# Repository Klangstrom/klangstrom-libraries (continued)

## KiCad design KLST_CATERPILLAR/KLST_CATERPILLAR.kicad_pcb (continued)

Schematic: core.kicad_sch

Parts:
C5, C10, C16, C28: 1uF; C_0402_1005Metric; JLCPCB C52923
C6, C7, C8, C11, C12, C14, C15, C17, C18, C19, C20, C21, C22, C23, C25: 100nF; C_0402_1005Metric; JLCPCB C1525
C9, C13: 12pF; C_0402_1005Metric; JLCPCB C1547
C24, C27: 2.2uF; C_0402_1005Metric; JLCPCB C107370
C26: 4.7uF; C_0402_1005Metric; JLCPCB C23733
D3: PWR_LED; LED_0805_2012Metric; JLCPCB C34499
R7: 10R; R_0402_1005Metric; JLCPCB C25077
R8: 1K; R_0805_2012Metric_Pad1.20x1.40mm_HandSolder; JLCPCB C17513
R9, R10, R11: 10K; R_0402_1005Metric; JLCPCB C25744
SW1: BUTTON_RESET; SW_Push_SPST_NO_Alps_SKRK; JLCPCB C115357
SW2: BUTTON_BOOT_FLASH; SW_Push_SPST_NO_Alps_SKRK; JLCPCB C115357
U2: STM32H723ZGTx; LQFP-144_20x20mm_P0.5mm; JLCPCB C730146
Y1: 16MHz; Crystal_SMD_3225-4Pin_3.2x2.5mm; JLCPCB C13738

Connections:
+3.3VA: C5.1, C7.1, C10.1, C12.1, U2.32 (VREF+), U2.33 (VDDA); also elsewhere on the board
/core/(PWR_LED): D3.1 (K), R8.2
/core/_PDR_ON: R10.2, U2.143 (PDR_ON)
/core/_VCAP_1: C24.1, U2.71 (VCAP)
/core/_VCAP_2: C27.1, U2.106 (VCAP)
BOOT0: R11.2, SW2.1, U2.138 (BOOT0)
GPIO_00_PWM: U2.13 (PF3); also elsewhere on the board
GPIO_02_PWM: U2.11 (PF1); also elsewhere on the board
GPIO_03_PWM: U2.10 (PF0); also elsewhere on the board
GPIO_04_ADC: U2.53 (PF13); also elsewhere on the board
GPIO_05_ADC: U2.49 (PF11); also elsewhere on the board
GPIO_06: U2.80 (PD11); also elsewhere on the board
GPIO_07: U2.14 (PF4); also elsewhere on the board
GPIO_08: U2.9 (PC15); also elsewhere on the board
GPIO_09: U2.8 (PC14); also elsewhere on the board
GPIO_10: U2.7 (PC13); also elsewhere on the board
GPIO_11: U2.134 (PB4(NJTRST)); also elsewhere on the board
GPIO_12: U2.118 (PD4); also elsewhere on the board
GPIO_13: U2.90 (PG5); also elsewhere on the board
GPIO_14: U2.89 (PG4); also elsewhere on the board
GPIO_15: U2.88 (PG3); also elsewhere on the board
GPIO_16: U2.87 (PG2); also elsewhere on the board
GPIO_17: U2.67 (PE14); also elsewhere on the board
GPIO_18: U2.117 (PD3); also elsewhere on the board
I2C_USR_SCL: U2.136 (PB6); also elsewhere on the board
I2C_USR_SDA: U2.137 (PB7); also elsewhere on the board
NRST: C25.1, R9.1, SW1.2, U2.25 (NRST); also elsewhere on the board
unnamed: C13.1, R7.2, Y1.3
SERIAL_USR_RX: U2.37 (PA3); also elsewhere on the board
SERIAL_USR_TX: U2.119 (PD5); also elsewhere on the board
SPI_USR_CS: U2.3 (PE4); also elsewhere on the board
SPI_USR_MISO: U2.4 (PE5); also elsewhere on the board
SPI_USR_MOSI: U2.5 (PE6); also elsewhere on the board
SPI_USR_SCK: U2.1 (PE2); also elsewhere on the board
_ADC_USR: U2.15 (PF5)
_AUDIO_CODEC_I2C_SCL: U2.54 (PF14); also elsewhere on the board
_AUDIO_CODEC_I2C_SDA: U2.55 (PF15); also elsewhere on the board
_AUDIO_CODEC_SAI_FS: U2.21 (PF9); also elsewhere on the board
_AUDIO_CODEC_SAI_MCLK: U2.19 (PF7); also elsewhere on the board
_AUDIO_CODEC_SAI_SCK: U2.20 (PF8); also elsewhere on the board
_AUDIO_CODEC_SAI_SD_IN: U2.48 (PB2); also elsewhere on the board
_AUDIO_CODEC_SAI_SD_OUT: U2.2 (PE3); also elsewhere on the board
_AUDIO_MIC_CLK: U2.28 (PC2_C); also elsewhere on the board
_AUDIO_MIC_DATA: U2.29 (PC3_C); also elsewhere on the board
_BUTTON_PROGRAMMER: U2.50 (PF12); also elsewhere on the board
_CARD_SDMMC_CK: U2.122 (PD6); also elsewhere on the board
_CARD_SDMMC_CMD: U2.123 (PD7); also elsewhere on the board
_CARD_SDMMC_D0: U2.124 (PG9); also elsewhere on the board
_CARD_SDMMC_D1: U2.125 (PG10); also elsewhere on the board
_CARD_SDMMC_D2: U2.126 (PG11); also elsewhere on the board
_CARD_SDMMC_D3: U2.127 (PG12); also elsewhere on the board
_DAC_USR: U2.40 (PA4)
_DISPLAY_BACKLIGHT_PWM: U2.98 (PC8)
_DISPLAY_LTDC_B0: U2.129 (PG14)
_DISPLAY_LTDC_B1: U2.114 (PD0)
_DISPLAY_LTDC_B2: U2.116 (PD2)
_DISPLAY_LTDC_B3: U2.79 (PD10)
_DISPLAY_LTDC_B4: U2.65 (PE12)
_DISPLAY_LTDC_B5: U2.135 (PB5)
_DISPLAY_LTDC_B6: U2.139 (PB8)
_DISPLAY_LTDC_B7: U2.140 (PB9)
_DISPLAY_LTDC_CLK: U2.92 (PG7)
_DISPLAY_LTDC_DE: U2.66 (PE13)
_DISPLAY_LTDC_G0: U2.47 (PB1)
_DISPLAY_LTDC_G1: U2.46 (PB0)
_DISPLAY_LTDC_G2: U2.42 (PA6)
_DISPLAY_LTDC_G3: U2.99 (PC9)
_DISPLAY_LTDC_G4: U2.69 (PB10)
_DISPLAY_LTDC_G5: U2.27 (PC1)
_DISPLAY_LTDC_G6: U2.97 (PC7)
_DISPLAY_LTDC_G7: U2.93 (PG8)
_DISPLAY_LTDC_HSYNC: U2.96 (PC6)
_DISPLAY_LTDC_R0: U2.128 (PG13)
_DISPLAY_LTDC_R1: U2.36 (PA2)
_DISPLAY_LTDC_R2: U2.111 (PC10)
_DISPLAY_LTDC_R3: U2.110 (PA15(JTDI))
_DISPLAY_LTDC_R4: U2.41 (PA5)
_DISPLAY_LTDC_R5: U2.26 (PC0)
_DISPLAY_LTDC_R6: U2.113 (PC12)
_DISPLAY_LTDC_R7: U2.68 (PE15)
_DISPLAY_LTDC_VSYNC: U2.43 (PA7)
_DISPLAY_ON_OFF: U2.44 (PC4)
_DISPLAY_TOUCH_INTERRUPT: U2.82 (PD13)
_ENCODER_00_A: U2.100 (PA8)
_ENCODER_00_B: U2.64 (PE11)
_ENCODER_00_BUTTON: U2.102 (PA10)
_ENCODER_01_A: U2.34 (PA0)
_ENCODER_01_B: U2.35 (PA1)
_ENCODER_01_BUTTON: U2.70 (PB11)
_EXT_MEMORY_A0: U2.73 (PB12)
_EXT_MEMORY_A1: U2.81 (PD12)
_EXT_MEMORY_A2: U2.74 (PB13)
_EXT_MEMORY_A3: U2.18 (PF6)
_EXT_MEMORY_A4: U2.58 (PE7)
_EXT_MEMORY_A5: U2.59 (PE8)
_EXT_MEMORY_A6: U2.60 (PE9)
_EXT_MEMORY_A7: U2.63 (PE10)
_EXT_MEMORY_CHIP_SELECT: U2.91 (PG6)
_EXT_MEMORY_CLK: U2.22 (PF10)
_EXT_MEMORY_DQS: U2.45 (PC5)
_IDC_SERIAL_00_RX: U2.141 (PE0); also elsewhere on the board
_IDC_SERIAL_00_TX: U2.142 (PE1); also elsewhere on the board
_IDC_SERIAL_01_RX: U2.56 (PG0)
_IDC_SERIAL_01_TX: U2.57 (PG1)
_LED_00: U2.75 (PB14); also elsewhere on the board
_LED_01: U2.76 (PB15); also elsewhere on the board
_MECH_BUTTON_00: U2.85 (PD14)
_MECH_BUTTON_01: U2.86 (PD15)
_MIDI_ANALOG_IN: U2.112 (PC11)
_MIDI_ANALOG_OUT: U2.115 (PD1)
_RCC_OSC_IN: C9.2, U2.23 (PH0), Y1.1
_RCC_OSC_OUT: R7.1, U2.24 (PH1)
_SERIAL_DEBUG_RX: U2.78 (PD9); also elsewhere on the board
_SERIAL_DEBUG_TX: U2.77 (PD8); also elsewhere on the board
_SWD_IO: U2.105 (PA13(JTMS)); also elsewhere on the board
_SWD_OUT: U2.133 (PB3(JTDO)); also elsewhere on the board
_USB_DEVICE_HOST_N: U2.103 (PA11); also elsewhere on the board
_USB_DEVICE_HOST_P: U2.104 (PA12); also elsewhere on the board
_USB_DEVICE_HOST_VBUS: U2.101 (PA9); also elsewhere on the board

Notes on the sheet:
CAP SPECS: CL=2*(CLOAD_XTAL-CPARASITIC) example: 12pF=2*(9pF-3pF)
@TODO(@maybe get rid of buttons)
VBAT: 1 μF ceramic and 100 nF close to the VBAT pin
@TODO(maybe PIN out fot GPIOs THT:C79866 or SMD:C601974/C2829932)
VDDA: 1 μF ceramic and 100 nF as close as possible of the pin.
press at startup for DFU mode. this is however usually done in software i.e this button is only necessary if something goes wrong
VDD1–11: 100 nF ceramic, for each VDD as close as possible of the pins. A 4.7 μF ceramic connected to one of the VDD pin.
PDR_ON tied to VDD = Power-on reset (POR) and power-down reset (PDR) circuit switched ON
MCU_POWER
BUTTON_RESET
@NOTE(close to MCU)
MCU
BUTTON_BOOT_FLASH
XTAL
POWER-LED

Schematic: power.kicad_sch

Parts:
C1, C2, C88, C89: 10uF; C_0805_2012Metric; JLCPCB C15850
C3, C69: 1uF; C_0805_2012Metric; JLCPCB C28323
C4, C71: 10nF; C_0805_2012Metric; JLCPCB C1710
FB1, FB4: 600Ω@100MHz; L_1206_3216Metric; JLCPCB C73732
L1, L4: 39nH; L_0402_1005Metric; JLCPCB C26443
NT1, NT2: NetTie_2; NetTie-2_SMD_Pad2.0mm; JLCPCB DNF
NT3: NetTie_2; NetTie-2_SMD_Pad0.5mm; JLCPCB DNF
Q1, Q4: AO3401A; SOT-23; JLCPCB C15127
U1: AMS1117-3.3; SOT-223-3_TabPin2; JLCPCB C6186
U14: AMS1117-1.8; SOT-223-3_TabPin2; JLCPCB C6185

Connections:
+1.8VA: C69.1, C71.1, L4.2; also elsewhere on the board
+3.3VA: C3.1, C4.1, L1.2; also elsewhere on the board
+5V: NT3.2, Q1.3 (D), Q4.3 (D); also elsewhere on the board
/power/(PWR_1.8V): C89.1, NT2.2, U14.2 (VO)
/power/(PWR_3.3V): C2.1, NT1.2, U1.2 (VO)
/power/(PWR_5V_TO_1.8V): C88.1, FB4.1, U14.3 (VI)
/power/(PWR_5V_TO_3.3V): C1.1, FB1.1, U1.3 (VI)
unnamed: FB1.2, Q1.2 (S)
unnamed: FB4.2, Q4.2 (S)
_USB_DEVICE_HOST_VBUS: NT3.1; also elsewhere on the board

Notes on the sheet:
VDDA can be connected to VDD through a ferrite bead. see AN5419
ANALOG POWER SUPPLY +1.8VA
USB POWER to 5V
@NOTE(200mA rating)
ANALOG POWER SUPPLY +3.3VA
POWER FLAGS
VOLTAGE REGULATOR +3.3V
needs to be added to power 5V rail from USB-C connector
VOLTAGE REGULATOR +1.8V

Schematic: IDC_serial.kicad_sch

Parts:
D18: SS14; D_SMA; JLCPCB C2480
J13: UART; IDC-Header_2x03_P2.54mm_Vertical_SMD; JLCPCB C492445

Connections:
+5V: J13.2; also elsewhere on the board
GPIO_00_PWM: J13.5; also elsewhere on the board

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
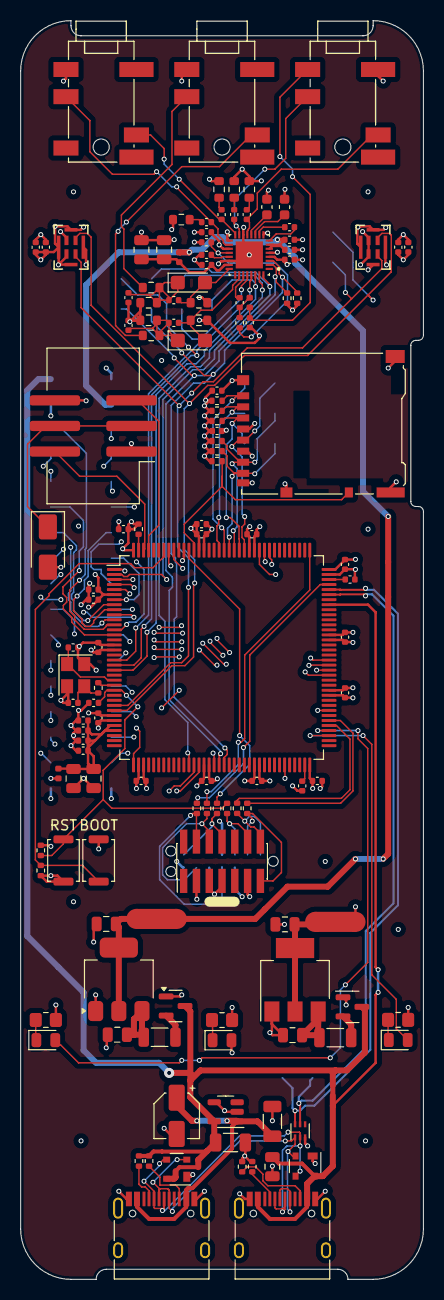
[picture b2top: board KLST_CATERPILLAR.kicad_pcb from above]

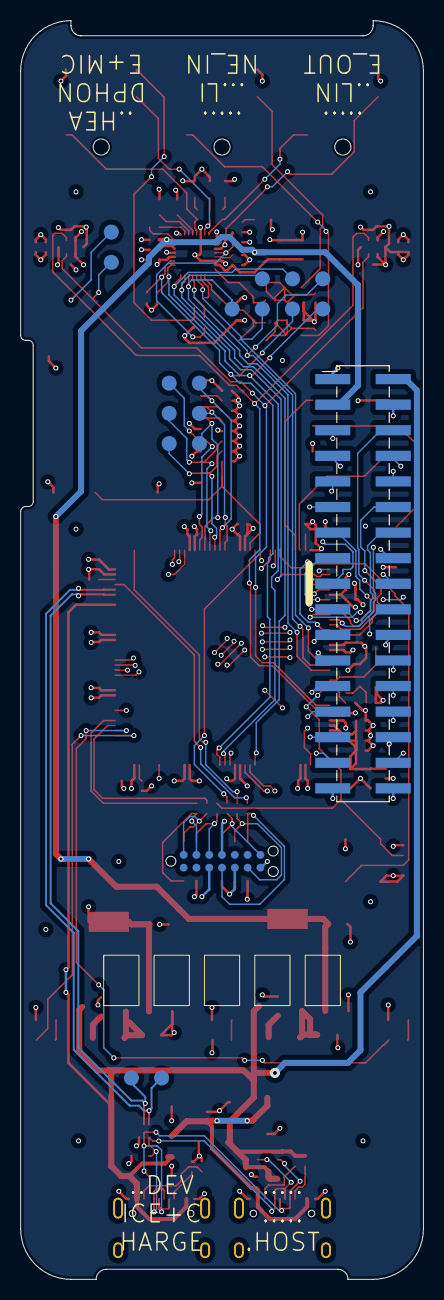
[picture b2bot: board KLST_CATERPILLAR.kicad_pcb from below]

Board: 6 copper layers, 40.0 x 125.0 mm, 154 parts (19 on the bottom side), 116 nets.

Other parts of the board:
D9: SS14; D_SMA
J5: UART; IDC-Header_2x03_P2.54mm_Vertical_SMD
R12: 10K; R_0402_1005Metric

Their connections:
_IDC_SERIAL_00_RX: J5.5; also elsewhere on the board
_IDC_SERIAL_00_TX: J5.2; also elsewhere on the board

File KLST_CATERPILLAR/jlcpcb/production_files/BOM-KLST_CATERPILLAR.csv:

Comment,Designator,Footprint,LCSC
2.2uF,"C24,C27",C_0402_1005Metric,C107370
Micro_SD_Card_Det_Hirose_DM3AT,J1,microSD_HC_Hirose_DM3AT-SF-PEJM5,C114218
47uF,C49,CP_Elec_4x5.4,C114447
22R,"R54,R55,R56,R57,R58,R59",R_0402_1005Metric,C114765
BUTTON_RESET,"SW1,SW2",SW_Push_SPST_NO_Alps_SKRK,C115357
LINE_IN,"J17,J18,J19",PJ-316A-6A,C128987
16MHz,Y1,Crystal_SMD_3225-4Pin_3.2x2.5mm,C13738
AO3401A,"Q1,Q4",SOT-23,C15127
100nF,"C11,C12,C14,C15,C17,C18,C19,C20,C21,C22,C23,C25,C30,C50,C6,C7,C77,C78,C79,C8,C80,C81,C83,C84,C87",C_0402_1005Metric,C1525
220pF,"C57,C60",C_0402_1005Metric,C1530
470pF,C58,C_0402_1005Metric,C1537
12pF,"C13,C9",C_0402_1005Metric,C1547
10uF,"C1,C2,C88,C89",C_0805_2012Metric,C15850
5Ω@100MHz,FB2,L_0402_1005Metric,C160969
HOST(DFP),"J10,J9",USB_C_Receptacle_HRO_TYPE-C-31-M-12,C165948
10nF,"C4,C71",C_0805_2012Metric,C1710
1K,"R1,R2,R8",R_0805_2012Metric_Pad1.20x1.40mm_HandSolder,C17513
4.7uF,"C26,C29,C72,C74,C85,C86",C_0402_1005Metric,C23733
SS14,D9,D_SMA,C2480
10R,R7,R_0402_1005Metric,C25077
10K,"R10,R11,R12,R13,R14,R15,R16,R17,R9",R_0402_1005Metric,C25744
39nH,"L1,L4",L_0402_1005Metric,C26443
ECMF02-2AMX6,U7,ST_UQFN-6L_1.5x1.7mm_P0.5mm,C2651144
MP34DT05TR-A,"U10,U11",MP34DT05TR-A_STM,C2688664
GPIO,J13,IDC-PinHeader_2x17_P2.54mm_Vertical_SMD,C2829932
1uF,"C3,C69",C_0805_2012Metric,C28323
ARM_JTAG_SWD(STDC14),J14,PinHeader_2x07_P1.27mm_Vertical_SMD,C2881912
10K,"R78,R79",R_0603_1608Metric,C2924143
100nF,"C47,C48",C_1206_3216Metric,C3015151
SP0503BAHT,"D12,D13",SOT-143,C3040626
1uF,C46,C_0805_2012Metric,C307362
WM8904CGEFL/V,U13,QFN40P400X400X80-33N,C323845
LED,"D1,D2,D3",LED_0805_2012Metric,C34499
56K,"R45,R46",R_0402_1005Metric,C352409
5.1K,"R43,R44",R_0402_1005Metric,C409730
5.6K,"R72,R73,R74,R77",R_0603_1608Metric,C417107
2.2uF,C70,C_0402_1005Metric,C452745
UART,J5,IDC-Header_2x03_P2.54mm_Vertical_SMD,C492445
TPS2041B,U8,SOT-23-5,C51386
1uF,"C10,C16,C28,C5,C51,C61,C64,C65,C82",C_0402_1005Metric,C52923
20R,"R80,R81,R82,R83",R_0603_1608Metric,C544033
AMS1117-1.8,U14,SOT-223-3_TabPin2,C6185
AMS1117-3.3,U1,SOT-223-3_TabPin2,C6186
10uF,"C63,C66",CP_EIA-3216-18_Kemet-A,C7171
STM32H723ZGTx,U2,LQFP-144_20x20mm_P0.5mm,C730146
600Ω@100MHz,"FB1,FB4",L_1206_3216Metric,C73732
2.2uF,"C67,C68",C_0603_1608Metric,C86013
2.2K,"R3,R4,R75",R_0402_1005Metric,C966835
TP_AUDIO_MIC_DATA,TP17,TestPoint_Pad_D1.5mm,
TP_AUDIO_MIC_CLK,TP16,TestPoint_Pad_D1.5mm,
TP_USB_DEVICE_HOST_P,TP15,TestPoint_Pad_D1.5mm,
TP_USB_DEVICE_HOST_N,TP14,TestPoint_Pad_D1.5mm,
TP_CARD_SDMMC_D1,TP13,TestPoint_Pad_D1.5mm,
TP_CARD_SDMMC_D0,TP12,TestPoint_Pad_D1.5mm,
TP_CARD_SDMMC_CK,TP11,TestPoint_Pad_D1.5mm,
TP_CARD_SDMMC_CMD,TP10,TestPoint_Pad_D1.5mm,
TP_CARD_SDMMC_D3,TP9,TestPoint_Pad_D1.5mm,
TP_CARD_SDMMC_D2,TP8,TestPoint_Pad_D1.5mm,
TP_AUDIO_CODEC_SAI_SD_IN,TP7,TestPoint_Pad_D1.5mm,
TP_AUDIO_CODEC_SAI_SD_OUT,TP6,TestPoint_Pad_D1.5mm,
TP_AUDIO_CODEC_SAI_SCK,TP5,TestPoint_Pad_D1.5mm,
TP_AUDIO_CODEC_SAI_FS,TP4,TestPoint_Pad_D1.5mm,
TP_AUDIO_CODEC_SAI_MCLK,TP3,TestPoint_Pad_D1.5mm,
TP_AUDIO_CODEC_I2C_SCA,TP2,TestPoint_Pad_D1.5mm,
TP_AUDIO_CODEC_I2C_SCL,TP1,TestPoint_Pad_D1.5mm,

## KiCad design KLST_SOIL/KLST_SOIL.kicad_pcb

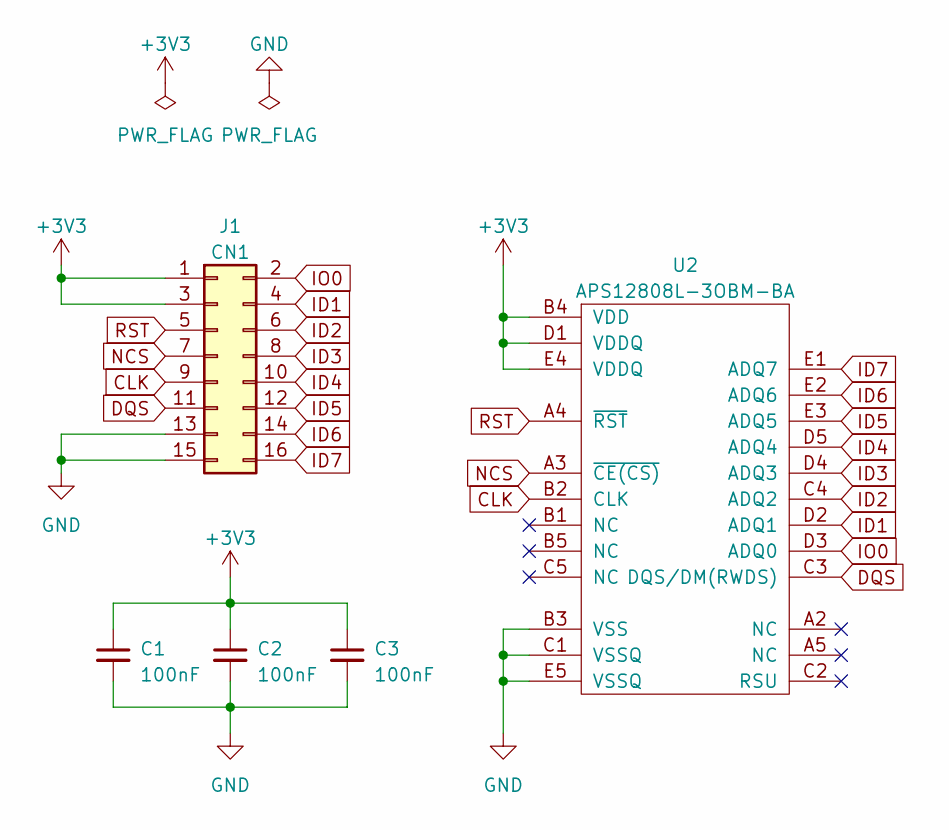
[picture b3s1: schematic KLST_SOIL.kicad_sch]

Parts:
C1, C2, C3: 100nF; C_0402_1005Metric
J1: CN1; PinSocket_2x08_P2.54mm_Vertical
U2: APS12808L-3OBM-BA

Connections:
+3V3: C1.1, C2.1, C3.1, J1.1, J1.3, U2.B4 (VDD), U2.D1 (VDDQ), U2.E4 (VDDQ)
CLK: J1.9, U2.B2 (CLK)
DQS: J1.11, U2.C3 (DQS/DM(RWDS))
GND: C1.2, C2.2, C3.2, J1.13, J1.15, U2.B3 (VSS), U2.C1 (VSSQ), U2.E5 (VSSQ)
ID1: J1.4, U2.D2 (ADQ1)
ID2: J1.6, U2.C4 (ADQ2)
ID3: J1.8, U2.D4 (ADQ3)
ID4: J1.10, U2.D5 (ADQ4)
ID5: J1.12, U2.E3 (ADQ5)
ID6: J1.14, U2.E2 (ADQ6)
ID7: J1.16, U2.E1 (ADQ7)
IO0: J1.2, U2.D3 (ADQ0)
NCS: J1.7, U2.A3 (~CE(CS))
RST: J1.5, U2.A4 (~RST)

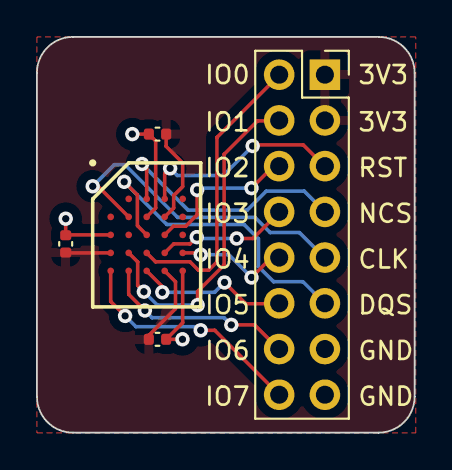
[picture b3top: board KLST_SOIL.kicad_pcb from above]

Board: 2 copper layers, 21.0 x 22.0 mm, 5 parts (0 on the bottom side), 14 nets.

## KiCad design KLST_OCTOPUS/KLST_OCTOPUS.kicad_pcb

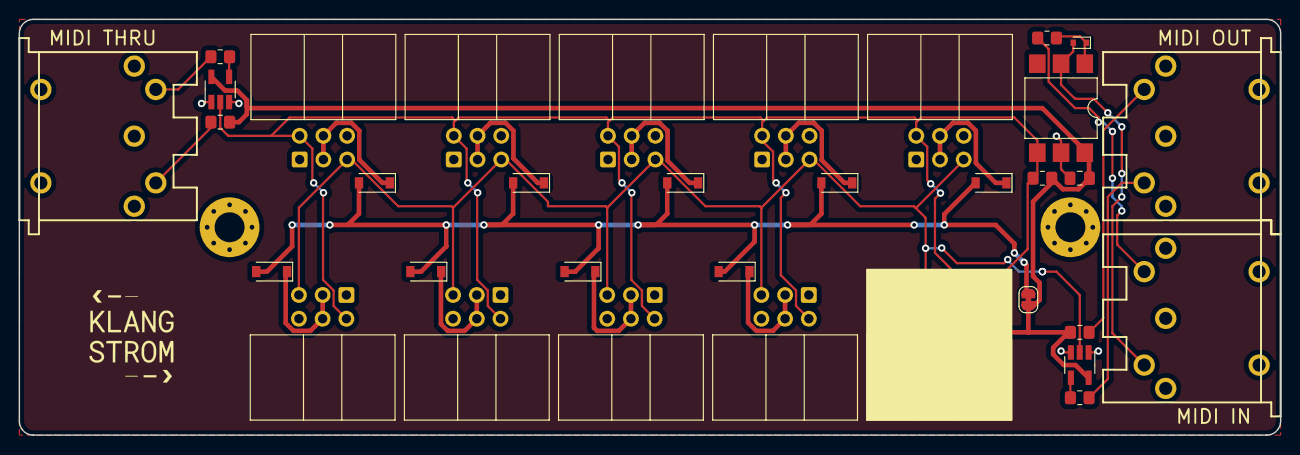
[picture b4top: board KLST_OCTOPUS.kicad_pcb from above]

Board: 2 copper layers, 135.0 x 44.5 mm, 37 parts (0 on the bottom side), 23 nets.

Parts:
C1: 100nF; C_0805_2012Metric_Pad1.18x1.45mm_HandSolder
D1: 1N914WT; D_SOD-523
D2, D3, D4, D5, D6, D7, D8, D9, D10: Schottky; D_SOD-123
H1, H2: MountingHole_Pad; MountingHole_3.2mm_M3_Pad_Via
J1: MIDI IN; DIN5-RA-PTH
J2: MIDI OUT; DIN5-RA-PTH
J3: MIDI THRU; DIN5-RA-PTH
J4, J5, J6, J7, J8, J9, J10, J11, J12, J13: UART; IDC-Header_2x03_P2.54mm_Horizontal
JP1: PWR; SolderJumper-2_P1.3mm_Bridged_RoundedPad1.0x1.5mm
R1, R2, R4, R5: 47; R_0805_2012Metric_Pad1.20x1.40mm_HandSolder
R3: 220; R_0805_2012Metric_Pad1.20x1.40mm_HandSolder
R6: 470; R_0805_2012Metric_Pad1.20x1.40mm_HandSolder
U1: H11L1SR2M; SMDIP-6_W9.53mm
U2, U3: 74AHC1G125; SOT-23-5_HandSoldering
X1: KLST_ICON; KLST--icon

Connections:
+3V3: C1.1, J4.3, J4.4, JP1.1 (A), R1.1, R2.1, R6.1, U1.6, U2.5 (VCC), U3.5 (VCC)
/PWR: D2.2 (A), D3.2 (A), D4.2 (A), D5.2 (A), D6.2 (A), D7.2 (A), D8.2 (A), D9.2 (A), D10.2 (A), JP1.2 (B)
/UART_RX: J4.2, J5.2, J6.2, J7.2, J8.2, J9.2, J10.2, J11.2, J12.2, J13.2, R6.2, U1.4, U3.2
/UART_TX: J4.5, J5.5, J6.5, J7.5, J8.5, J9.5, J10.5, J11.5, J12.5, J13.5, U2.2
GND: C1.2, J2.2, J3.2, J4.1, J4.6, J5.1, J5.6, J6.1, J6.6, J7.1, J7.6, J8.1, J8.6, J9.1, J9.6, J10.1, J10.6, J11.1, J11.6, J12.1, J12.6, J13.1, J13.6, U1.5, U2.1, U2.3 (GND), U3.1, U3.3 (GND)
unnamed: D1.1 (K), R3.2, U1.1
unnamed: D1.2 (A), J1.5, U1.2
unnamed: D2.1 (K), J5.3, J5.4
unnamed: D3.1 (K), J6.3, J6.4
unnamed: D4.1 (K), J7.3, J7.4
unnamed: D5.1 (K), J8.3, J8.4
unnamed: D6.1 (K), J9.3, J9.4
unnamed: D7.1 (K), J10.3, J10.4
unnamed: D8.1 (K), J11.3, J11.4
unnamed: D9.1 (K), J12.3, J12.4
unnamed: D10.1 (K), J13.3, J13.4
unnamed: J1.4, R3.1
unnamed: J2.4, R1.2
unnamed: J2.5, R4.1
unnamed: J3.4, R2.2
unnamed: J3.5, R5.1
unnamed: R4.2, U2.4
unnamed: R5.2, U3.4

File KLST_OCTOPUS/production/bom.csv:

Designator,Footprint,Quantity,Value,LCSC Part #
C1,C_0805_2012Metric_Pad1.18x1.45mm_HandSolder,1,100nF,C49678 
D1,D_SOD-523,1,1N914WT,C896167
"D10, D2, D3, D4, D5, D6, D7, D8, D9",D_SOD-123,9,Schottky,C8598
"H1, H2",MountingHole_3.2mm_M3_Pad_Via,2,MountingHole_Pad,
J1,DIN5-RA-PTH,1,MIDI IN,C2939344
"J10, J11, J12, J13, J4, J5, J6, J7, J8, J9",IDC-Header_2x03_P2.54mm_Horizontal,10,UART,C146629
J2,DIN5-RA-PTH,1,MIDI OUT,C2939344
J3,DIN5-RA-PTH,1,MIDI THRU,C2939344
JP1,SolderJumper-2_P1.3mm_Bridged_RoundedPad1.0x1.5mm,1,PWR,
"R1, R2, R4, R5",R_0805_2012Metric_Pad1.20x1.40mm_HandSolder,4,47,C328398
R3,R_0805_2012Metric_Pad1.20x1.40mm_HandSolder,1,220,C479094
R6,R_0805_2012Metric_Pad1.20x1.40mm_HandSolder,1,470,C328396
U1,SMDIP-6_W9.53mm,1,H11L1SR2M,C20082
"U2, U3",SOT-23-5_HandSoldering,2,74AHC1G125,C5513

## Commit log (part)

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2024-02-04 started LTDC
2024-02-04 LCD clears background now … but does not update
2024-02-04 LCD works now with DMA2D
    … not exactly sure what i am doing here though ;)
2024-02-04 backlight dimming works now
2024-02-04 minor changes
2024-02-05 imporved OCTO-SPI performance
2024-02-05 managed to get VSYNC synchronization to work
2024-02-05 reduced to one layer
2024-02-06 added double buffering,
2024-02-06 adapted display timing to ST7282 datasheet
2024-02-07 moved modules to dedicated files
2024-02-08 added touch panel support
2024-02-09 added KLST_SHEEP firmware
2024-02-09 added audiocodec
2024-02-09 tried to get audiocodec to work
2024-02-10 audiocodec still not working
2024-02-11 audiocodec produces trash sound with MCLK ( at least something )
2024-02-12 hell!!!
2024-02-12 clean up, still not working
2024-02-13 fixed D-chache issue with DMA
2024-02-14 added SAI4 + BDMA
2024-02-15 added CRC + PDM
2024-02-15 PDM mic not working yet
2024-02-16 PDM MIC still silent :(
2024-02-17 started encoders ( in C++ ), minor changes
2024-02-18 added SDCard support ( no DMA )
2024-02-18 started mechanical keys
2024-02-18 mechanical key work, MECH_00 and TOUCH via GPIO_EXTI and MECH_01 via TIM4
2024-02-19 added module configuration
2024-02-19 started MIDI analog
2024-02-19 started adding IDC ( still not working :( )
2024-02-20 fixed project file, still struggling with UART
2024-02-21 struggling with UART … still
2024-02-21 added buffer to UART ( still only semi functional )
2024-02-22 adde coding style, added rotary encoder,
2024-02-25 enabled DMA for SD Card
2024-02-25 cleaned up MIDI
2024-02-25 updated kicad files to 8.0
2024-02-26 added USB Host, enabled DMA for UART4+9 ( but not using it yet )
2024-02-26 added USB Device ( but deactivated )
2024-02-26 moved MIDI to own file
2024-02-27 added ADC + DAC
2024-02-27 still struggling with MIDI
2024-02-28 final got MIDI to work ( not sure if it is now TYPE A or B ;) )
2024-02-29 MIDI(TRS-TypeA) works now, added note on/off
2024-02-29 added display off when not used
2024-03-01 added on board mic files, deleted linker script *RAM.ld
2024-03-06 added report, update pin map
2024-03-06 added comments
2024-03-06 generate separate files for peripherals
2024-03-06 started BSP implementation
2024-03-07 started rearranging peripherals
2024-03-11 rearranged klangstrom
2024-03-11 added klangstrom sources
2024-03-11 prepared submodule
2024-03-11 added klangstrom-libraries as submodule
2024-03-13 added +1.8V power, removed SS14, added decoupling capacitor to MEMS mic
2024-03-13 added DFSDM channels + filters
2024-03-13 removed SAI from on-board mic
2024-03-14 tweaked dfsdm
2024-03-14 removed SS14, moved `SPI_USR` to `SPI4` use `SPI2` for MEMS microphones, added decoupling caps to MEMS microphone, added +1.8V, fixed audio codec power supply
2024-03-14 corrected GPIOs
2024-03-15 added KLST_CATERPILLAR
2024-03-15 changed project name
2024-03-15 reduced modules
2024-03-15 finished placing components
2024-03-15 routed modules ( not finished )
2024-03-16 added jlcpcb production files
2024-03-16 added GPIOs
2024-03-17 added test points, replaced unavailable components
2024-03-17 updated via drill hole size to 3mm
2024-03-28 added note to connnect USB to 5V when without battery
2024-03-28 fixed: connected 5V to USB power
2024-03-28 added net tie for USB to 5V
2024-05-06 updated H7 FW to 1.11.2
2024-05-06 removed "has a LOAD segment with RWX permissions" warning
2024-05-08 started cleaning up
2024-05-08 updated submodule
2024-05-09 removed worms, cleaned up
2024-05-09 extracted audiocodec
2024-05-10 added LL callback to audiocodec
2024-05-13 update environment constants
2024-05-14 added copy of STM32duino variant definition
2024-05-14 added script to symlink variant files
2024-05-14 added script to develop variant with STM32duino
2024-05-27 updated shell script to generate absolute symlinks
2024-05-27 added script to link libraries
2024-05-27 cleaned up firmware, audio codec now works with ARDUINO IDE
2024-05-28 moved KLST_PANDA_STM32 to own library
2024-05-28 cleaned up init + setup
2024-05-28 added LED, fixed print+println
2024-05-30 started adding KLST_EMU implementations
2024-05-30 added audio codec callback for emulator
2024-05-31 audiocodec callback can now either use uint32 or float
2024-05-31 silenced compiler warnings
2024-06-02 added functions test
2024-06-02 added LED view
2024-06-03 added audiocodec view
2024-06-03 added input view
2024-06-04 added `KLST_ARCH_IS_` define, removed warnings
2024-06-08 added SD Card ( not working ), added FatFS
2024-06-09 SD Card now works in STM32CubeIDE but not arduino
2024-06-09 started adding KLST_CATERPILLAR variant ( pure arduino )
2024-06-09 fix interrupt functions
2024-06-11 added boards.txt, add pin definitions
2024-06-11 added CMake files ( generated by CLion )
2024-06-12 added CMake
2024-06-13 undef’d FatFs
2024-06-13 added SD card to DMA setup
2024-07-03 prepared KLST_PANDA_STM32 for cmake
2024-07-03 removed emulator include
2024-07-03 fixed example
2024-07-04 separated generated source files
2024-07-04 moved tools to klangstrom-stm32
2024-07-05 added #endif
2024-07-06 added tools back in again ( will archive entire project soon )
2024-07-06 added filelist for script
2024-07-06 formatted code with clang-format
2024-07-06 generated + formatted with script
2024-07-06 fixed CMake to propagate KLST_ENV
2024-07-09 updated copyright
2024-07-09 fixed warnings, updated formatting
2024-07-09 added external mic
2024-07-28 added device type, removed `KLANG_*` defines
2024-07-29 added `Callback Dispatcher Pattern` in coding style, started interpreting audio info
2024-07-29 made mutex optional for emulator
2024-07-29 reworked mutext
2024-07-30 fixed KSLT_PANDA audio codec (again)
2024-07-30 fixed console
2024-08-02 started reworking libraries to C-based style
2024-08-02 transition to C-style (WIP)
2024-08-02 starting from scratch now implementing all peripherals C-style
2024-08-02 added console
2024-08-04 cleaned up and improved audio codec
2024-08-04 cleaned up audio device/codec
2024-08-05 improved and optimized console
2024-08-05 reworked audio codec in C-style
2024-08-05 added config file (WIP)
2024-08-06 added LEDs, added SDCard support
2024-08-06 added SDCard to EMU
2024-08-07 added audio stream from SDCard example, implemented timestamp
2024-08-07 fixed file reading
2024-08-08 added options for format
2024-08-09 added serial to EMU
2024-08-09 added serial (UART), added tick,
2024-08-09 finally got SD card audio streaming to work
2024-08-10 added option to slow down SD card initialization phase, made SD card a bit less verbose ( for normal operations )
2024-08-10 added cycle counter + clock freq (WIP), added DMA pool size, cleaned up
2024-08-11 cleaned up serial
2024-08-11 added clock cycles and ticks, added (U)ID (WIP)
2024-08-12 started introducing KLST_CATERPILLAR
2024-08-12 added LED, audiodevice, SD card and IDC serial to KLST_CATERPILLAR
2024-08-12 updated ASCII art
2024-08-12 added display, added external memory
2024-08-12 removed A/BSP prefix
2024-08-13 fixed baud rate, struggled with UART, added MIDI
2024-08-15 updated generated code
2024-08-16 removed USB from klangstromm added USB Device as library
2024-08-16 added USB Device
2024-08-16 removed USB Device
2024-08-16 added USBHost as library
2024-08-17 added HID MIDI support to host
2024-08-17 fixed minor bugs, formatted code
2024-08-17 USB Host is now working for MIDI
2024-08-17 added rotary encoder
2024-08-17 renamed rotary encoder to encoder, added callbacks to encoder
2024-08-18 freed TIM4
2024-08-18 added advanced example for custom GPIO pin, added option to trigger external interrupt for all 16 GPIO pins
2024-08-18 started adding internal microphone
2024-08-19 added microphone
2024-08-19 added DAC + ADC
2024-08-20 added CMSIS DSP library
2024-08-20 display is now working in single/double buffer mode ( with 60Hz animation ) and touch panel and backlight
2024-08-22 WIP … but DMA2D interaction is slowly improving
2024-08-22 puuuh struggling with DMA2D drawing … implemented a software renderer for now.
2024-08-22 LTDC can switch renderer, touch panel can be deactivated
2024-08-22 first naive attempt at ordering interrupts
2024-08-23 playing with interrupts … no success :(
2024-08-24 changed drill hole size to 0.3
2024-08-25 replaced out-of-stock resistors, excluded cherry keys from BOM
2024-08-25 added 3D model
2024-08-25 moved on-off switch
2024-08-27 cleaned up LTDC, added more primitives and fonts
2024-08-27 added modes to touch panel, made touch panel more robust ( tries to recover )
2024-08-27 tried to use ADC in DMA mode ( not working )
2024-08-30 cleaned up draw library
2024-08-30 added scalable pixel fonts
2024-08-31 implenting Display
2024-08-31 fixed pixel allpha blending
2024-08-31 added display on/off
2024-09-02 reworked timer and beat for STM32
2024-09-02 cleaned up timer
2024-09-03 fixed Beat, cleaned up
2024-09-03 fixed display example
2024-09-03 ADC now uses DMA ( implementation needs some serious tuning )
2024-09-04 added adc to KLST_CATERPILLAR
2024-09-04 added klangwellen example
2024-09-06 added READMEs, added options to change buffer sizes, fixed output in arduino-cli emulator,
2024-09-07 added examples connecting to external devices
2024-09-23 production ready for V2
2024-09-23 production commit for v2.0
2024-11-24 fixed examples
2024-12-04 removed errors, added mounting holes for LCD, added 傲慢と無知
2024-12-13 production commit for v2.1
2025-01-05 fixed KLST_TINY reversed diode, minor changes to KLST_PANDA
2025-01-09 added key to emulator
2025-01-09 added key BSP
2025-01-14 added UID for KLST_PANDA
2025-09-04 added emulator as library
2025-09-04 cleaned up emulator
2025-09-04 Squashed 'libraries/' changes from 3d3af03..c6f215e
    c6f215e cleaned up emulator
    b7e60bb added emulator as library
    d748dd1 Merge branch 'main' of https://github.com/dennisppaul/klangstrom-libraries
    339a914 Merge branch 'main' of https://github.com/dennisppaul/klangstrom-libraries
    0f47687 Merge branch 'main' of https://github.com/dennisppaul/klangstrom-libraries
    4b85322 Merge branch 'main' of https://github.com/dennisppaul/klangstrom-libraries
2025-09-08 revived basic emulator operation
2025-09-08 Squashed 'libraries/' changes from c6f215e..d036338
    d036338 revived basic emulator operation
    git-subtree-dir: libraries
    git-subtree-split: d036338530ef9d1d5fd4049b35c0ea266565c545
2025-09-10 changed backlight PWM frequency
2025-09-10 Squashed 'libraries/' changes from d036338..d0cd72a
    d0cd72a changed backlight PWM frequency
    git-subtree-dir: libraries
    git-subtree-split: d0cd72aea27642fa9eaa1a06ed8d2ddcecb2fa56
2025-09-12 moved old projects to attic
2025-09-13 renamed color macros, cleaned up custom peripherals
2025-09-13 started WAV example
2025-09-13 cleaned up install script
2025-09-13 Squashed 'libraries/' changes from d0cd72a..537c9d2
    537c9d2 updated copyright
    82055eb minor changes
    d55a6f3 started WAV example
    12b4eca renamed color macros, cleaned up custom peripherals
    git-subtree-dir: libraries
    git-subtree-split: 537c9d2738835e36942af5144ee46876c1ffdf95
2025-09-14 changed license, removed attic, update logotype
2025-09-14 cleaned up URLs
2025-09-14 removed libs as submodule
2025-09-15 removed stale workflow
2025-09-15 added clang format and tidy
2025-09-15 fixed BYTES_PER_PIXEL
2025-09-15 fixed color
2025-09-18 added stand alone, added example
2025-09-18 fixed emulator
2025-09-19 WIP audio processing
2025-09-19 WIP fixed audio input
2025-09-19 improved audio device
2025-09-19 fixed WAVE example
2025-09-19 (WIP) plating WAV files
2025-09-20 moved arduino functions to core
2025-09-20 cleaned up WAV reader
2025-09-20 updated examples for audio and display ( squeezed ext_mem and display into play WAV example (WIP) )
2025-09-21 added external memory allocation, moved emulator widgets a bit
2025-09-22 fix: linux compat
2025-09-22 renamed Timer to PeriodicTimer
2025-09-23 added UID to emulator, added image + char to emulator
2025-09-23 fixed example, added display example
2025-09-23 removed OSC sources
2025-09-23 started implementing encoder emulator
2025-09-24 made callback const
2025-09-24 added color functions, fixed examples, added script to test examples
2025-09-27 fixed examples, improved hardware timer precision in emulator
2025-09-30 added templated map function, added example for external memory, fixed ext mem size in emulator
